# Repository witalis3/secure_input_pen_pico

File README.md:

# secure_input_pen
# secure_input_pen_pico

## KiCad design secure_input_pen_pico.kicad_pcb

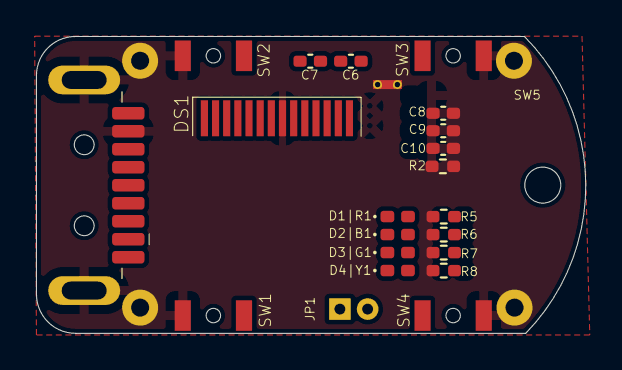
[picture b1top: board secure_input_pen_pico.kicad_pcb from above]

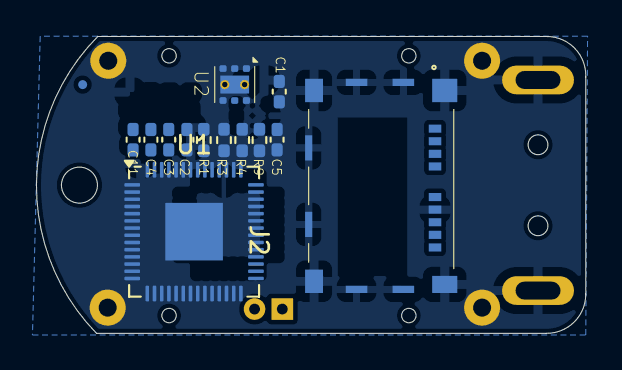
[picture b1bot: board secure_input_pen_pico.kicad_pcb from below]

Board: 6 copper layers, 30.5 x 16.5 mm, 40 parts (14 on the bottom side), 27 nets, no tracks yet.

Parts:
C1, C4, C5: 100nF; C_0402_1005Metric_Pad0.74x0.62mm_HandSolder
C2, C3, C6, C7, C10, C11: 1uF; C_0402_1005Metric_Pad0.74x0.62mm_HandSolder
C8, C9: 2,2uF; C_0402_1005Metric_Pad0.74x0.62mm_HandSolder
D1|R1, D2|B1, D3|G1, D4|Y1: LED; LED_0402_1005Metric_Pad0.77x0.64mm_HandSolder
DS1: OLED-60O032D
H1, H2, H3, H4: MountingHole_Pad; MountingHole_1mm_Pad
H5: MountingHole; MountingHole_2mm
J1: USB3_A; USB3_A_Plug_Wuerth_692112030100_Horizontal
J2: MEM2085-00-115-00-A_REV0.2; GCT_MEM2085-00-115-00-A_REV0.2
JP1: boot; PinHeader_1x02_P2.54mm_Vertical
R1, R3, R4: 4,7k; R_0402_1005Metric_Pad0.72x0.64mm_HandSolder
R2: 220k; R_0402_1005Metric_Pad0.72x0.64mm_HandSolder
R5, R7, R8: 220; R_0402_1005Metric_Pad0.72x0.64mm_HandSolder
R6: 68; R_0402_1005Metric_Pad0.72x0.64mm_HandSolder
R9: 1M; R_0402_1005Metric_Pad0.72x0.64mm_HandSolder
SW1, SW2, SW3, SW4: B3U-3000P; SW_SPST_B3U-3000P-B
SW5: sensor dotykowy; conn_touch
U1: RP2040; QFN-56-1EP_7x7mm_P0.4mm_EP3.2x3.2mm
U2: LP5912-3.3DRV; WSON-6-1EP_2x2mm_P0.65mm_EP1x1.6mm_ThermalVias

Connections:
/+3,3V: C1.1, C3.1, C5.1, C10.1, C11.1, DS1.5 (VBAT), DS1.8 (VDD), J2.P4 (VDD), JP1.2 (B), R1.1, R3.1, R4.1, R5.1, R6.1, R7.1, R8.1, R9.1, U2.1 (OUT)
/+5V: C2.1, J1.1 (VBUS), U2.4 (EN), U2.6 (IN)
/D+: J1.3 (D+), U1.47 (USB_DP)
/D-: J1.2 (D-), U1.46 (USB_DM)
/SCL: DS1.10 (SCL), R3.2
/SDA: DS1.11 (SDA), R4.2
/SW1: SW1.1, U1.9 (GPIO7)
/SW2: SW2.2, U1.11 (GPIO8)
/SW3: SW3.1, U1.12 (GPIO9)
/SW4: SW4.2, U1.13 (GPIO10)
/reset: C4.1, U1.26 (RUN)
unnamed: D1|R1.2 (A), R5.2
unnamed: D2|B1.2 (A), R6.2
unnamed: D3|G1.2 (A), R7.2
unnamed: D4|Y1.2 (A), R8.2
unnamed: C7.2, DS1.4 (C1N)
unnamed: C7.1, DS1.3 (C1P)
unnamed: C6.2, DS1.2 (C2N)
unnamed: C6.1, DS1.1 (C2P)
unnamed: DS1.12 (IREF), R2.1
unnamed: C8.1, DS1.14 (VCC)
unnamed: C9.1, DS1.13 (VCOMH)
unnamed: R9.2, SW5.1
unnamed: U1.23 (DVDD), U1.50 (DVDD)
unnamed: U1.1 (IOVDD), U1.10 (IOVDD), U1.22 (IOVDD), U1.33 (IOVDD), U1.42 (IOVDD), U1.49 (IOVDD)
unnamed: R1.2, U2.3 (PG)
masa: C1.2, C2.2, C3.2, C4.2, C5.2, C8.2, C9.2, C10.2, C11.2, DS1.7 (VSS), H1.1, H2.1, H3.1, H4.1, J1.4 (GND), J1.10 (SHIELD), J2.G1 (GND), J2.G2 (GND), J2.G3 (GND), J2.G4 (GND), J2.G5 (GND), J2.G6 (GND), J2.G7 (GND), J2.G8 (GND), J2.G9 (GND), J2.G10 (GND), J2.P6 (VSS), R2.2, SW1.2, SW2.1, SW3.2, SW4.1, U1.57 (GND), U2.5 (GND), U2.7 (EP)

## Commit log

2025-07-11 must message #1
2025-07-11 projekt PCB
2025-07-11 Exploits
